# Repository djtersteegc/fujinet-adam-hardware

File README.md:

After building a few of [mozzwald's](https://mozzwald.com/) original [FujiNet](https://fujinet.online/fujinet/) for [Coleco ADAM](https://fujinet.online/fujinet/#ColecoADAM) boards, I decided I wanted to create a new SMD version that was a bit quicker to assemble for folks building them in quantity, but still sticking with the ESP32-Devkit-C-VE board and larger 0805 sized components for the DIY crowd. Both boards are single sided for easy assembly, with the only through hole parts being the RJ12 jack(s), LED's, and the devkit board itself. In the end I ended up with two different designs, one I'm calling the Devkit SMD and the other the Devkit Mini.

# Devkit SMD

Similar to the original design, this one offers two ADAMNet ports to daisy chain other devices, but instead of a microSD slot, now offers a full size SD card.

You can build it in two different configurations, one using 8.5mm female headers for the devkit board, similar to the original.  This gives the options of reusing the ESP32 for something else in the future and easy access to the SMD components underneath it.  If you are confident in your soldering skills and want something more compact, you can also build it with the ESP board soldered directly to the main PCB on 3mm spaces.

See the [Devkit SMD page](fujinet-adam-devkit-smd/README.md) for BOM and assembly instructions.

# Devkit Mini

This was an exercise in can I make a full FujiNet fit in the space of the devkit PCB. For that I had to go back to a microSD slot and it only supports one ADAMNet port.

See the [Devkit Mini page](fujinet-adam-devkit-mini/README.md) for BOM and assembly instructions.

# Getting a Bare Board or Assembled Unit

Any extras I have available will be in my [Tindie](https://www.tindie.com/stores/tersteeg/) store. I don't ship outside the US currently, but gerber files are available for both boards if you want to order your own from your favorite PCB fab like JLCPCB or PCBWay.

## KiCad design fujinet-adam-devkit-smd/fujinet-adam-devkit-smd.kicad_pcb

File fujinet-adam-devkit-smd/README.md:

# Schematic

https://djtersteegc.github.io/fujinet-adam-hardware/fujinet-adam-devkit-smd-schematic-v1.3.pdf

# BOM

There's an interactive BOM [here](https://djtersteegc.github.io/fujinet-adam-hardware/ibom-devkit-smd.html), I find them super useful when placing the SMD parts. 

I buy pretty much everything from AliExpress suppliers with the exception of the tantalum capacitors (whatever is on clearance at Newark) and the ESP32 board (cheaper shipped from Amazon). If you are bulding in the "tall" configuration, you will also need some 2.54mm female headers.  I buy the 1x40p models and break when down into two 19 pin headers required by the devkit board.

C2 is a bulk storage cap for the 5V input from the ADAMNet line.  I speced it at 100uF, but anything from 22uF and up will probably be fine.  You may not even really need it.

C1 is to handle inrush and prevent sag and MCU reboots on the 3.3V rail if you are hot swapping your SD card.  Mozzwald's original design went without, so not strictly needed, especially if you don't plan on hot swapping the card.

| Component                           | Qty  | Notes                      | Link                                                         |
| ----------------------------------- | ---- | -------------------------- | ------------------------------------------------------------ |
| 47uF 10V 3528 Tantalum Capacitor    | 1    | B Type Case (or smaller)   | [AliExpress](https://www.aliexpress.us/item/2251832779546992.html) |
| 100uF 10V 7343 Tantalum Capacitor   | 1    | E Type Case (or smaller)   | [AliExpress](https://www.aliexpress.us/item/2251832782845246.html) |
| 10K 0805 Resistor                   | 11   |                            | [AliExpress](https://www.aliexpress.us/item/3256801607747550.html) |
| 1K 0805 Resistor                    | 4    |                            | [AliExpress](https://www.aliexpress.us/item/3256801607747550.html) |
| 2K 0805 Resistor                    | 2    |                            | [AliExpress](https://www.aliexpress.us/item/3256801607747550.html) |
| 4.7K 0805 Resistor                  | 2    |                            | [AliExpress](https://www.aliexpress.us/item/3256801607747550.html) |
| 1.2K 0805 Resistor                  | 1    |                            | [AliExpress](https://www.aliexpress.us/item/3256801607747550.html) |
| 33R 0805 Resistor                   | 1    |                            | [AliExpress](https://www.aliexpress.us/item/3256801607747550.html) |
| B140 SMA DO-214 Schottky Diode      | 2    | SS14 also works            | [AliExpress](https://www.aliexpress.us/item/2255800145156429.html) |
| 3mm LED (Blue)                      | 1    | Bluetooth                  | [AliExpress](https://www.aliexpress.us/item/2255800226600744.html) |
| 3mm LED (White)                     | 1    | Wifi                       | [AliExpress](https://www.aliexpress.us/item/2255800226600744.html) |
| 3mm LED (Orange)                    | 1    | Activity                   | [AliExpress](https://www.aliexpress.us/item/2255800226600744.html) |
| Alps SKRK Style Switch              | 3    | 3x4x2mm                    | [AliExpress](https://www.aliexpress.us/item/2255801131587911.html) |
| MMBT3904 SOT-23                     | 1    |                            | [AliExpress](https://www.aliexpress.us/item/3256802985590487.html) |
| MMBT3906 SOT-23                     | 1    |                            | [AliExpress](https://www.aliexpress.us/item/3256802985563795.html) |
| RJ12 Amphenol 54601                 | 2    | 95001-6P6C on Ali          | [AliExpress](https://www.aliexpress.us/item/3256802891796239.html) |
| SD Card TE 2041021                  | 1    | Long Body on Ali           | [AliExpress](https://www.aliexpress.us/item/3256805779248826.html) |
| ESP32-Devkit-C-VE                   | 1    |                            | [Amazon](https://www.amazon.com/dp/B087TNPQCV)               |
| 2.54mm 19p 8.5mm Tall Female Header | 2    | "Tall" option build only   | [AliExpress](https://www.aliexpress.us/item/2251832484668248.html) |
| SK12D07VG4 Slide Switch             | 1    | Optional power SW for v1.2 | [AliExpress](https://www.aliexpress.us/item/3256806549741426.html) |

# Flashing

I like to program the ESP32 first to ensure I have a good unit before soldering them onto the main PCB. Since this uses the same devkit board as the "official" model, you can use the FujiNet firmware flasher available at https://fujinet.online/download/. 

# Assembly

Lay down all the SMD components first.  When complete, your board shoud look like this.

Next decide if you are building it on female headers or soldering the devkit directly to the board.  If the latter, there are some 3mm spacers and support blocks in the "short" 3D directory you can print out to space the devkit board correctly and keep the board level when you flip it over to solder it together.

Next solder on the two RJ12 jacks.  For the LED's, I first insert them in the PCB, then the PCB in the case, flip it over and support the case ~1mm off the surface for the LED's to just poke through the top and get a nice reveal. Solder one leg on the LED's, flip it over to check your spacing again, and then solder the other leg.

# Case

If built on female headers, print the files in the "tall" directory.  Make sure to print three buttons.  If soldering directly to the board spaced 3mm above it, use the case file in the "short" directory.  Assemble with two M2.5x10mm screws.

PCB version 1.2 adds the ability to install a power switch if you want to disable the Fuji in your ADAMNet chain without unplugging it.

If you are printing with a multi color AMS enabled printer, you can use the embossed-text STL files to color fill the top text.

# PCB Revisions

### Version 1.0

Working, but the second RJ12/ADAMNet connector was incorrectly wired in the schematic and does not work as intended.  I assumed straight through when it should have been reversed, hence the RJ12 cross over cables used on the ADAM. Fortunately, the fix is pretty simple and by luck of the ground planes, you don't even need to remove the RJ12 connector.

These the PCB traces you need to cut (black X's).

Three are on the top between the two RJ12 jacks.  I used an Xacto blade. Be careful of the trace immediately above the top one connecting the 3.3V rail of the LED's.  I nicked the one in this example, but it was still connected.  Worst case, you need to add another wire to bodge D2 to D3.

Then you need to seperate the Pin 5 (lower right in the photo) on the back from the four ground plane thermal relief connections.

Finally you need to connect J2 to the correct pins on J1. 

| J1 - ADAMNet In | J2 - ADAMNet Out |
| --------------- | ---------------- |
| 1 (Data)        | 6 (Data)         |
| 2 (Reset)       | 5 (Reset)        |
| 3 (GND)         | 4 (GND)          |
| 4 (GND)         | 3 (GND)          |
| 5 (GND)         | 2 (GND)          |
| 6 (5V)          | 1 (5V)           |

Since pin 3 and pin 4 on J2 are alreay connected to ground nothing to do there.  You can connect Pin 2 which is now GND to Pin 4.  The remaining three pins need bodge wires over to J1.  Here's what it should look like completed.

Check the connections from J1 to J2 and ensure the 5V line in particular it not shorted to GND.  Plug into the Adam to confirm all is now working with the keyboard plugged into the AdamNET Out (left most) port on the Fujinet.

### Version 1.1

All good

### Version 1.2

Adds an optional power switch.  If you don't want to install the swtich, bridge the Always On solder jumper.

### Version 1.3

Rotated the LED footprints 90 degrees so the legs bend easier when inserting and removing from the case.

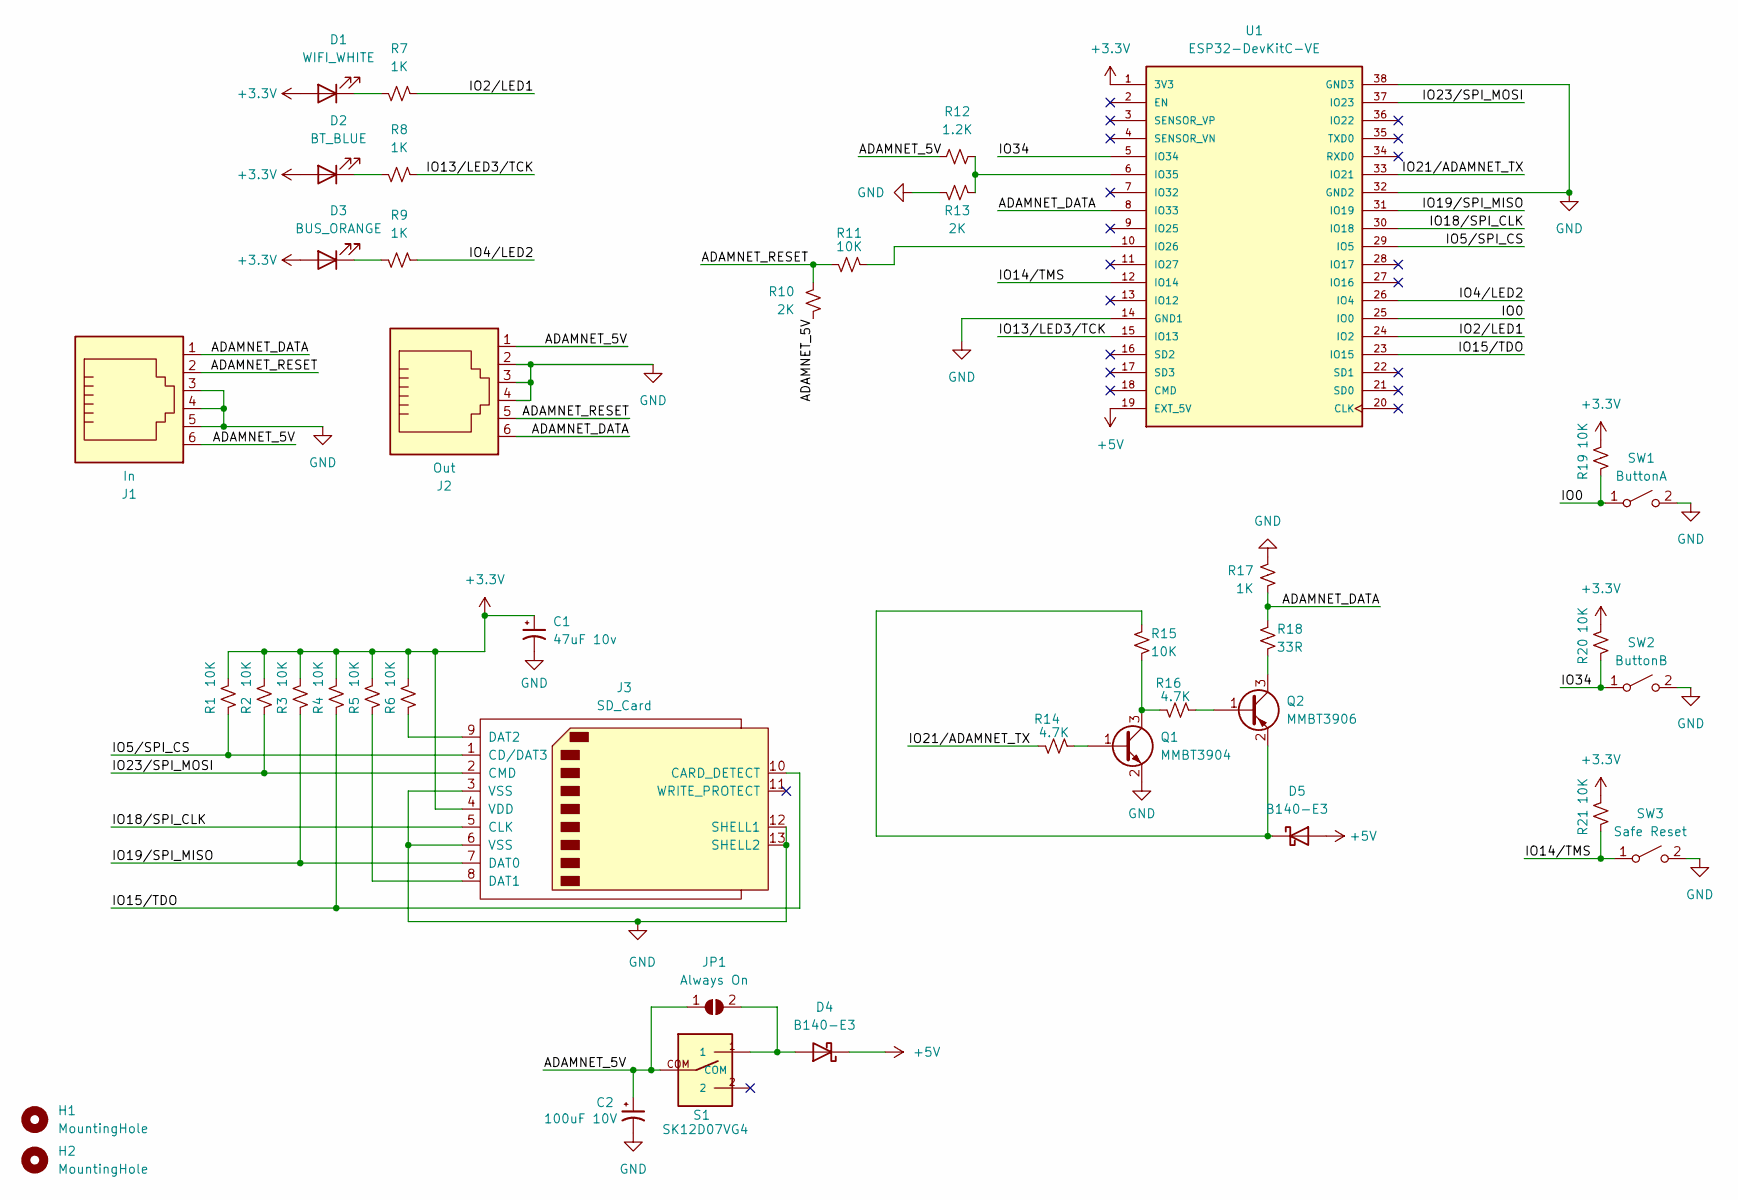
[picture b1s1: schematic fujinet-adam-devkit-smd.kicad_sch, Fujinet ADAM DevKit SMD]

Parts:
C1: 47uF 10v; CP_EIA-3528-15_AVX-H_Pad1.50x2.35mm_HandSolder
C2: 100uF 10V; CP_EIA-7343-20_Kemet-V_Pad2.25x2.55mm_HandSolder
D1: WIFI_WHITE; LED_D3.0mm
D2: BT_BLUE; LED_D3.0mm
D3: BUS_ORANGE; LED_D3.0mm
D4, D5: B140-E3; D_SMA
H1, H2: MountingHole; MountingHole_2.7mm_M2.5
J1: In; RJ12_Amphenol_54601
J2: Out; RJ12_Amphenol_54601
J3: SD_Card; SD_TE_2041021
JP1: Always On; SolderJumper-2_P1.3mm_Open_RoundedPad1.0x1.5mm
Q1: MMBT3904; SOT-23
Q2: MMBT3906; SOT-23
R1, R2, R3, R4, R5, R6, R11, R15, R19, R20, R21: 10K; R_0805_2012Metric_Pad1.20x1.40mm_HandSolder
R7, R8, R9, R17: 1K; R_0805_2012Metric_Pad1.20x1.40mm_HandSolder
R10, R13: 2K; R_0805_2012Metric_Pad1.20x1.40mm_HandSolder
R12: 1.2K; R_0805_2012Metric_Pad1.20x1.40mm_HandSolder
R14, R16: 4.7K; R_0805_2012Metric_Pad1.20x1.40mm_HandSolder
R18: 33R; R_0805_2012Metric_Pad1.20x1.40mm_HandSolder
S1: SK12D07VG4
SW1: ButtonA; SW_Push_SPST_NO_Alps_SKRK
SW2: ButtonB; SW_Push_SPST_NO_Alps_SKRK
SW3: Safe Reset; SW_Push_SPST_NO_Alps_SKRK
U1: ESP32-DevKitC-VE; MODULE_ESP32-DEVKITC-32U; PARTREV N/A

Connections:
+3.3V: C1.1, D1.2 (A), D2.2 (A), D3.2 (A), J3.4 (VDD), R1.2, R2.2, R3.2, R4.2, R5.2, R6.2, R19.2, R20.2, R21.2, U1.1 (3V3)
+5V: D4.1 (K), D5.2 (A), U1.19 (EXT_5V)
/ADAMNET_5V: C2.1, J1.6, J2.1, JP1.1 (A), R10.1, R12.1, S1.COM
/ADAMNET_DATA: J1.1, J2.6, R17.1, R18.2, U1.8 (IO33)
/ADAMNET_RESET: J1.2, J2.5, R10.2, R11.1
/IO0: R19.1, SW1.1 (A), U1.25 (IO0)
/IO2/LED1: R7.2, U1.24 (IO2)
/IO4/LED2: R9.2, U1.26 (IO4)
/IO5/SPI_CS: J3.1 (CD/DAT3), R1.1, U1.29 (IO5)
/IO13/LED3/TCK: R8.2, U1.15 (IO13)
/IO14/TMS: R21.1, SW3.1 (A), U1.12 (IO14)
/IO15/TDO: J3.10 (CARD_DETECT), R4.1, U1.23 (IO15)
/IO18/SPI_CLK: J3.5 (CLK), U1.30 (IO18)
/IO19/SPI_MISO: J3.7 (DAT0), R3.1, U1.31 (IO19)
/IO21/ADAMNET_TX: R14.2, U1.33 (IO21)
/IO23/SPI_MOSI: J3.2 (CMD), R2.1, U1.37 (IO23)
/IO34: R20.1, SW2.1 (A), U1.5 (IO34)
GND: C1.2, C2.2, J1.3, J1.4, J1.5, J2.2, J2.3, J2.4, J3.3 (VSS), J3.6 (VSS), J3.12 (SHELL1), J3.13 (SHELL2), Q1.2 (E), R13.1, R17.2, SW1.2 (B), SW2.2 (B), SW3.2 (B), U1.14 (GND1), U1.32 (GND2), U1.38 (GND3)
unnamed: D1.1 (K), R7.1
unnamed: D2.1 (K), R8.1
unnamed: D3.1 (K), R9.1
unnamed: D4.2 (A), JP1.2 (B), S1.1
unnamed: D5.1 (K), Q2.2 (E), R15.2
unnamed: J3.8 (DAT1), R5.1
unnamed: J3.9 (DAT2), R6.1
unnamed: Q1.1 (B), R14.1
unnamed: Q1.3 (C), R15.1, R16.2
unnamed: Q2.1 (B), R16.1
unnamed: Q2.3 (C), R18.1
unnamed: R11.2, U1.10 (IO26)
unnamed: R12.2, R13.2, U1.6 (IO35)

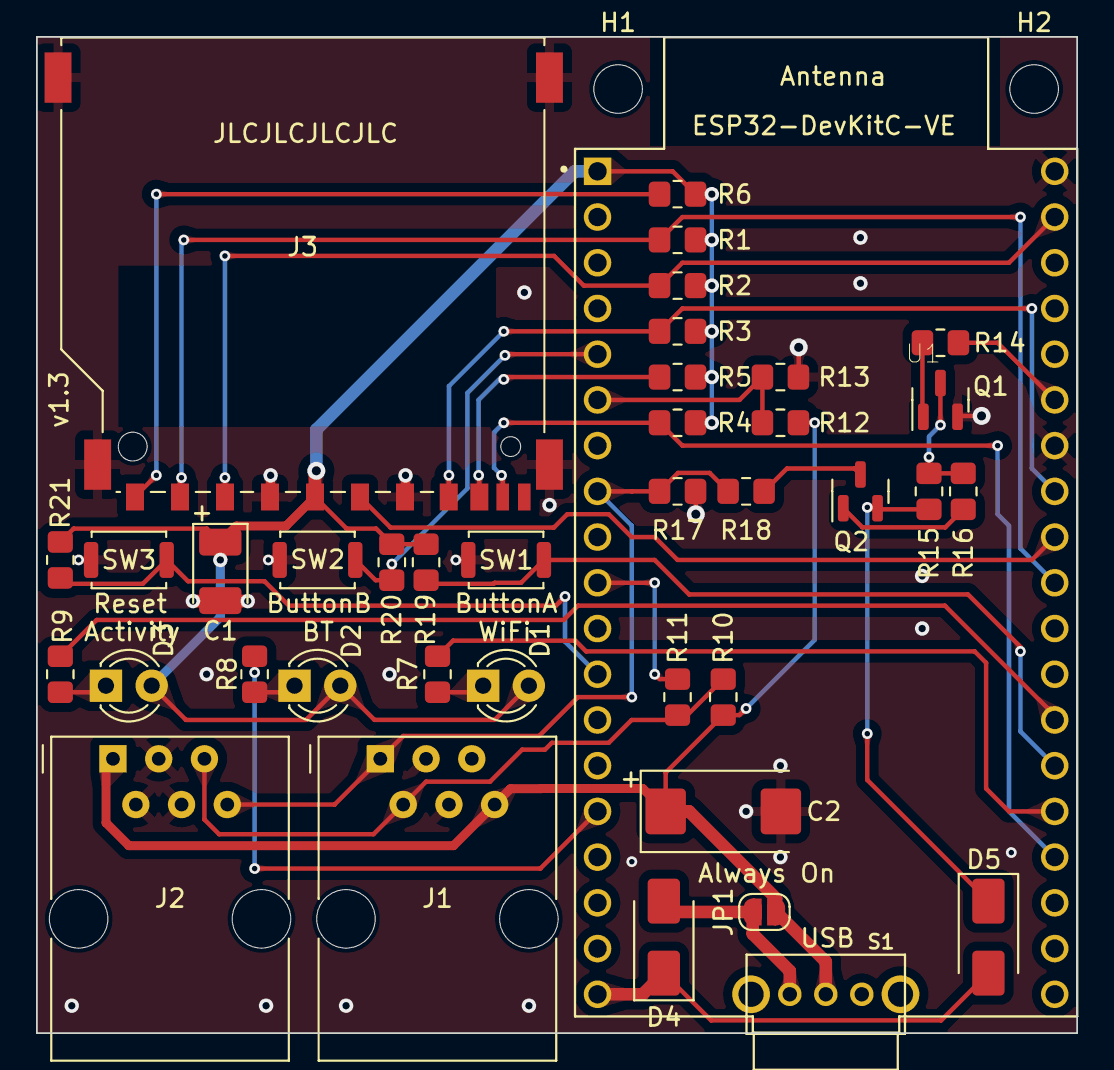
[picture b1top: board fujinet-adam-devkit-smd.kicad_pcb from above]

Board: 2 copper layers, 57.8 x 55.3 mm, 41 parts (0 on the bottom side), 31 nets.

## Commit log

2023-11-11 Add some docs
2023-11-11 Update README's
2023-11-11 Add tall SMD pic
2023-11-11 Update docs
2023-11-12 Fix Mini BOM in README
2023-11-12 Add additional build hints for the Mini
2023-12-25 Add rework cut pic
2023-12-26 Add rework instructions for second RJ12 port on SMD version.
2023-12-26 Update SMD PCB and Case to v1.1, fix ADAMNet Out port not working
2023-12-26 v1.1 PCB tweak
2024-11-24 Add SMD version 1.2 PCB/case files and embossed text STL's for AMS printing
2024-11-24 Add missing image
2026-01-02 Update SMD version to 1.3 Add tall case for versions with a power switch
